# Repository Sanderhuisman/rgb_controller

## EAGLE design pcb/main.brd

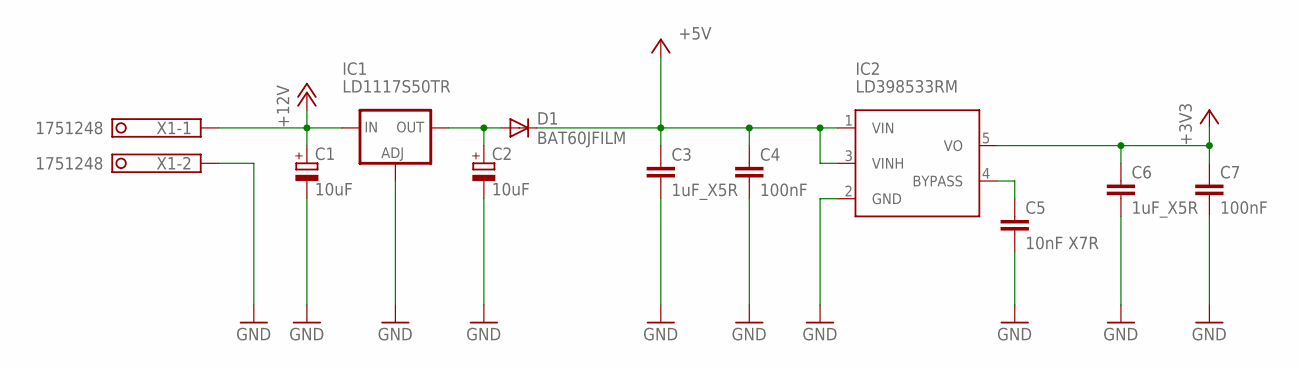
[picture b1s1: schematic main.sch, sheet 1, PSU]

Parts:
C1, C2: 10uF; SMC_C
C3, C6: 1uF_X5R; C0805
C4, C7: 100nF; C0805
C5: 10nF X7R; C0805
D1: BAT60JFILM; SOD323-W
IC1: LD1117S50TR; SOT223
IC2: LD398533RM; SOT23-5L
X1: 1751248

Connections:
+3V3: C6.1, C7.1, IC2.5 (VO); also elsewhere on the board
+5V: C3.1, C4.1, D1.C, IC2.1 (VIN), IC2.3 (VINH); also elsewhere on the board
+12V: C1.+, IC1.3 (IN), X1.1; also elsewhere on the board
GND: C1.-, C2.-, C3.2, C4.2, C5.2, C6.2, C7.2, IC1.1 (ADJ), IC2.2 (GND), X1.2; also elsewhere on the board
unnamed: C2.+, D1.A, IC1.4 (OUT)
unnamed: C5.1, IC2.4 (BYPASS)

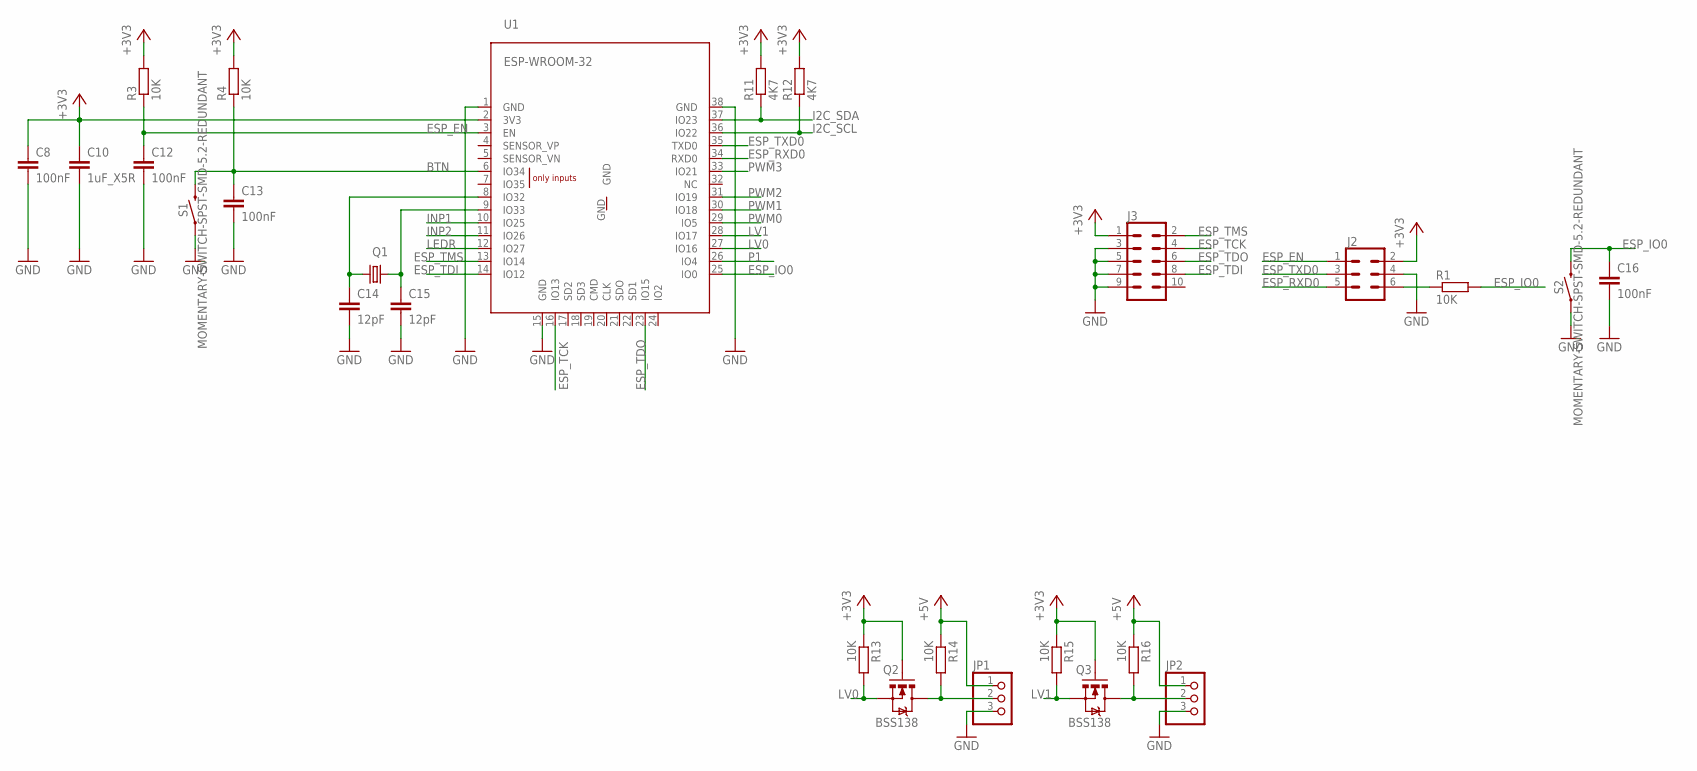
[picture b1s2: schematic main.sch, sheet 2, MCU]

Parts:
C8, C12, C13, C16: 100nF; C0805
C10: 1uF_X5R; C0805
C14, C15: 12pF; C0805
J2: CONN_03X2SHROUD; 2X3-SHROUDED
J3: CONN_05X2SHD; 2X5-SHROUDED
JP1, JP2: PINHD-1X3; 1X03
Q1: CRYSTALTC38H; TC38H
Q2, Q3: BSS138; SOT23-3
R1, R3, R4, R13, R14, R15, R16: 10K; R0805
R11, R12: 4K7; R0805
S1, S2: MOMENTARY-SWITCH-SPST-SMD-5.2-REDUNDANT; TACTILE_SWITCH_SMD_5.2MM
U1: ESP-WROOM-32

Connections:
+3V3: C8.1, C10.1, J2.2, J3.1, Q2.1 (G), Q3.1 (G), R3.2, R4.2, R11.2, R12.2, R13.1, R15.1, U1.2 (3V3); also elsewhere on the board
+5V: JP1.1, JP2.1, R14.1, R16.1; also elsewhere on the board
BTN: C13.1, R4.1, S1.3 (2), S1.4 (2), U1.6 (IO34)
ESP_EN: C12.1, J2.1, R3.1, U1.3 (EN)
ESP_IO0: C16.1, R1.2, S2.3 (2), S2.4 (2), U1.25 (IO0)
ESP_RXD0: J2.5, U1.34 (RXD0)
ESP_TCK: J3.4, U1.16 (IO13)
ESP_TDI: J3.8, U1.14 (IO12)
ESP_TDO: J3.6, U1.23 (IO15)
ESP_TMS: J3.2, U1.13 (IO14)
ESP_TXD0: J2.3, U1.35 (TXD0)
GND: C8.2, C10.2, C12.2, C13.2, C14.2, C15.2, C16.2, J2.4, J3.3, J3.5, J3.7, J3.9, JP1.3, JP2.3, S1.1, S1.2 (1), S2.1, S2.2 (1), U1.1 (GND), U1.15 (GND), U1.38 (GND); also elsewhere on the board
HV1: JP1.2, Q2.3 (D), R14.2
HV2: JP2.2, Q3.3 (D), R16.2
I2C_SCL: R12.1, U1.36 (IO22); also elsewhere on the board
I2C_SDA: R11.1, U1.37 (IO23); also elsewhere on the board
INP1: U1.10 (IO25); also elsewhere on the board
INP2: U1.11 (IO26); also elsewhere on the board
LEDR: U1.12 (IO27); also elsewhere on the board
LV0: Q2.2 (S), R13.2, U1.27 (IO16)
LV1: Q3.2 (S), R15.2, U1.28 (IO17)
unnamed: J2.6, R1.1
unnamed: C14.1, Q1.2, U1.8 (IO32)
unnamed: C15.1, Q1.1, U1.9 (IO33)
P1: U1.26 (IO4); also elsewhere on the board
PWM0: U1.29 (IO5); also elsewhere on the board
PWM1: U1.30 (IO18); also elsewhere on the board
PWM2: U1.31 (IO19); also elsewhere on the board
PWM3: U1.33 (IO21); also elsewhere on the board

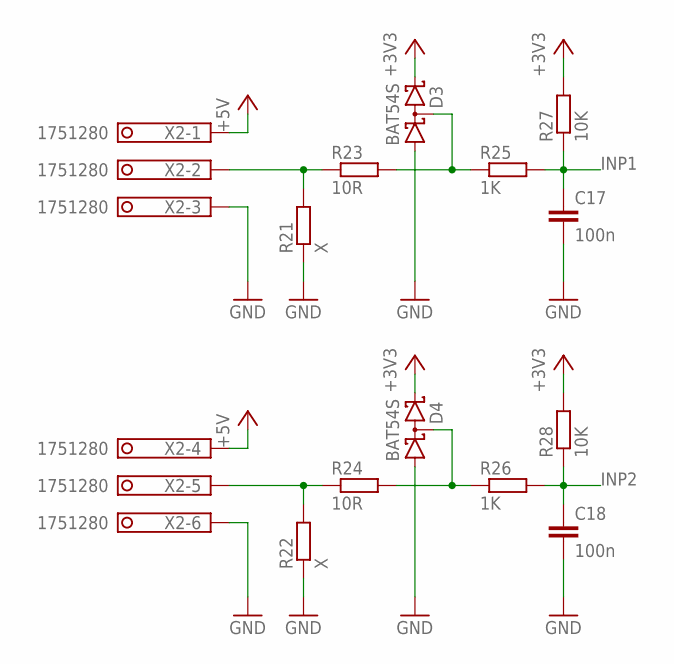
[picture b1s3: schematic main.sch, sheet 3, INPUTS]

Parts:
C17, C18: 100n; C0805
D3, D4: BAT54S; SOT23
R21, R22: X; R0805
R23, R24: 10R; R0805
R25, R26: 1K; R0805
R27, R28: 10K; R0805
X2: 1751280

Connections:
+3V3: D3.2 (C2), D4.2 (C2), R27.2, R28.2; also elsewhere on the board
+5V: X2.1, X2.4; also elsewhere on the board
GND: C17.2, C18.2, D3.1 (A1), D4.1 (A1), R21.1, R22.1, X2.3, X2.6; also elsewhere on the board
INP1: C17.1, R25.2, R27.1; also elsewhere on the board
INP2: C18.1, R26.2, R28.1; also elsewhere on the board
unnamed: R22.2, R24.1, X2.5
unnamed: D3.3 (C1A2), R23.2, R25.1
unnamed: D4.3 (C1A2), R24.2, R26.1
unnamed: R21.2, R23.1, X2.2

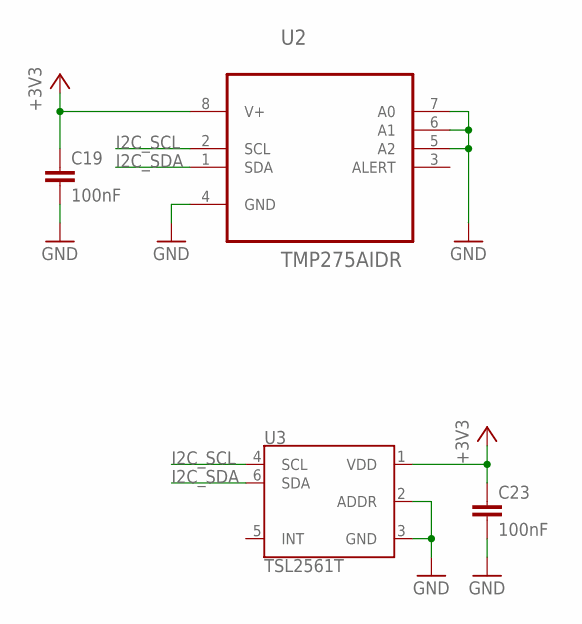
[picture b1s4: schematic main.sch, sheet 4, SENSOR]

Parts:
C19, C23: 100nF; C0805
U2: TMP275AIDR; SOIC127P600X175-8N
U3: TSL2561T; TMB-6

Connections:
+3V3: C19.1, C23.1, U2.8 (V+), U3.1 (VDD); also elsewhere on the board
GND: C19.2, C23.2, U2.4 (GND), U2.5 (A2), U2.6 (A1), U2.7 (A0), U3.2 (ADDR), U3.3 (GND); also elsewhere on the board
I2C_SCL: U2.2 (SCL), U3.4 (SCL); also elsewhere on the board
I2C_SDA: U2.1 (SDA), U3.6 (SDA); also elsewhere on the board

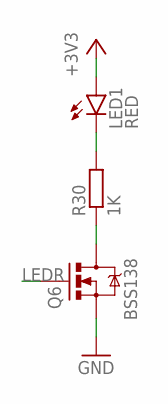
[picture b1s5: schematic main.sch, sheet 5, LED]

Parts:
LED1: RED; CHIPLED_0805
Q6: BSS138; SOT23-3
R30: 1K; R0805

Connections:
+3V3: LED1.A; also elsewhere on the board
GND: Q6.2 (S); also elsewhere on the board
LEDR: Q6.1 (G); also elsewhere on the board
unnamed: Q6.3 (D), R30.2
unnamed: LED1.C, R30.1

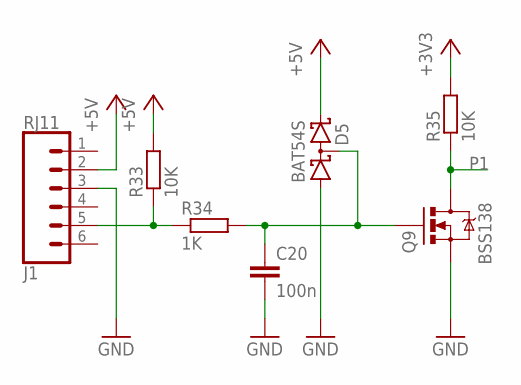
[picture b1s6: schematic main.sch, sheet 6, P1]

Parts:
C20: 100n; C0805
D5: BAT54S; SOT23
J1: RJ11; RJ11-6
Q9: BSS138; SOT23-3
R33, R35: 10K; R0805
R34: 1K; R0805

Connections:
+3V3: R35.2; also elsewhere on the board
+5V: D5.2 (C2), J1.2, R33.2; also elsewhere on the board
GND: C20.2, D5.1 (A1), J1.3, Q9.2 (S); also elsewhere on the board
unnamed: J1.5, R33.1, R34.1
unnamed: C20.1, D5.3 (C1A2), Q9.1 (G), R34.2
P1: Q9.3 (D), R35.1; also elsewhere on the board

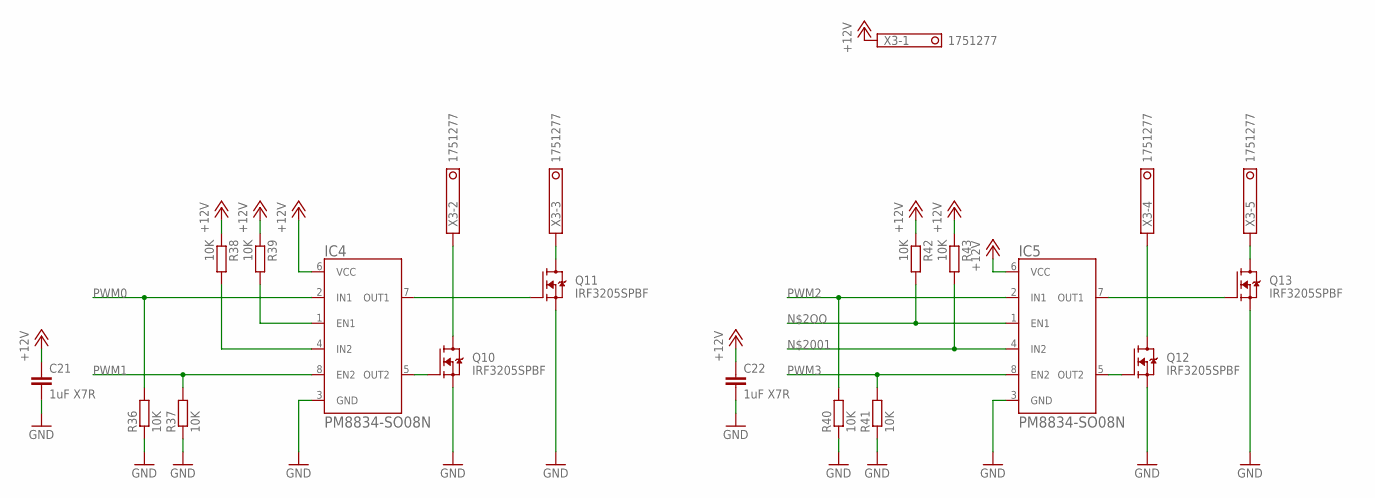
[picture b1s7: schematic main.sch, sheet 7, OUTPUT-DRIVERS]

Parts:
C21, C22: 1uF X7R; C0805
IC4, IC5: PM8834-SO08N; SO08N
Q10, Q11, Q12, Q13: IRF3205SPBF; TRANS_IRF3205SPBF
R36, R37, R38, R39, R40, R41, R42, R43: 10K; R0805
X3: 1751277

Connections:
+12V: C21.1, C22.1, IC4.6 (VCC), IC5.6 (VCC), R38.2, R39.2, R42.2, R43.2, X3.1; also elsewhere on the board
GND: C21.2, C22.2, IC4.3 (GND), IC5.3 (GND), Q10.3 (S), Q11.3 (S), Q12.3 (S), Q13.3 (S), R36.2, R37.2, R40.2, R41.2; also elsewhere on the board
unnamed: IC5.1 (EN1), R42.1
unnamed: Q10.2 (D), X3.2
unnamed: IC4.1 (EN1), R39.1
unnamed: IC4.4 (IN2), R38.1
unnamed: IC4.7 (OUT1), Q11.1 (G)
unnamed: IC4.5 (OUT2), Q10.1 (G)
unnamed: Q11.2 (D), X3.3
unnamed: IC5.7 (OUT1), Q13.1 (G)
unnamed: IC5.5 (OUT2), Q12.1 (G)
unnamed: Q12.2 (D), X3.4
unnamed: Q13.2 (D), X3.5
unnamed: IC5.4 (IN2), R43.1
PWM0: IC4.2 (IN1), R36.1; also elsewhere on the board
PWM1: IC4.8 (EN2), R37.1; also elsewhere on the board
PWM2: IC5.2 (IN1), R40.1; also elsewhere on the board
PWM3: IC5.8 (EN2), R41.1; also elsewhere on the board

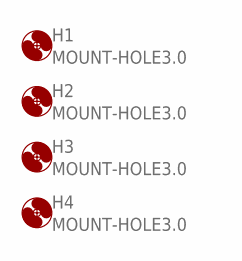
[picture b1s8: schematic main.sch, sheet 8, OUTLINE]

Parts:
H1, H2, H3, H4: MOUNT-HOLE3.0; 3,0

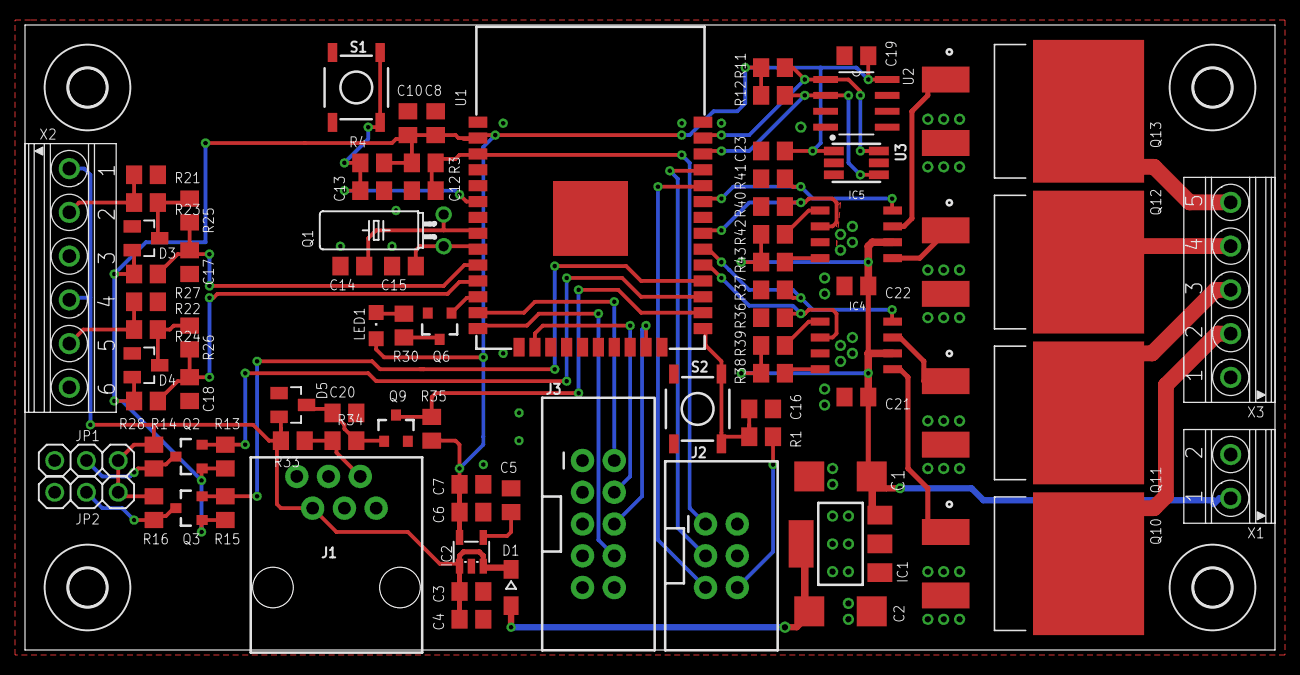
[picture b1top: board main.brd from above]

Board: 2 copper layers, 100.0 x 50.0 mm, 85 parts (0 on the bottom side), 52 nets.

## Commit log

2019-02-20 Initial project
2019-02-21 Added UART and further work on schematics
2019-02-22 Smaller MCU updated schematics
2019-02-22 Added temperature sensor
2019-02-23 Renamed project
2019-03-20 Layouting and update
2019-03-24 Layouting
2019-10-12 ESP wroom module
2020-03-03 backup

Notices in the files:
parts and their libraries:
SparkFun-Switches: Licensing: Creative Commons ShareAlike 4.0 International - https://creativecommons.org/licenses/by-sa/4.0
